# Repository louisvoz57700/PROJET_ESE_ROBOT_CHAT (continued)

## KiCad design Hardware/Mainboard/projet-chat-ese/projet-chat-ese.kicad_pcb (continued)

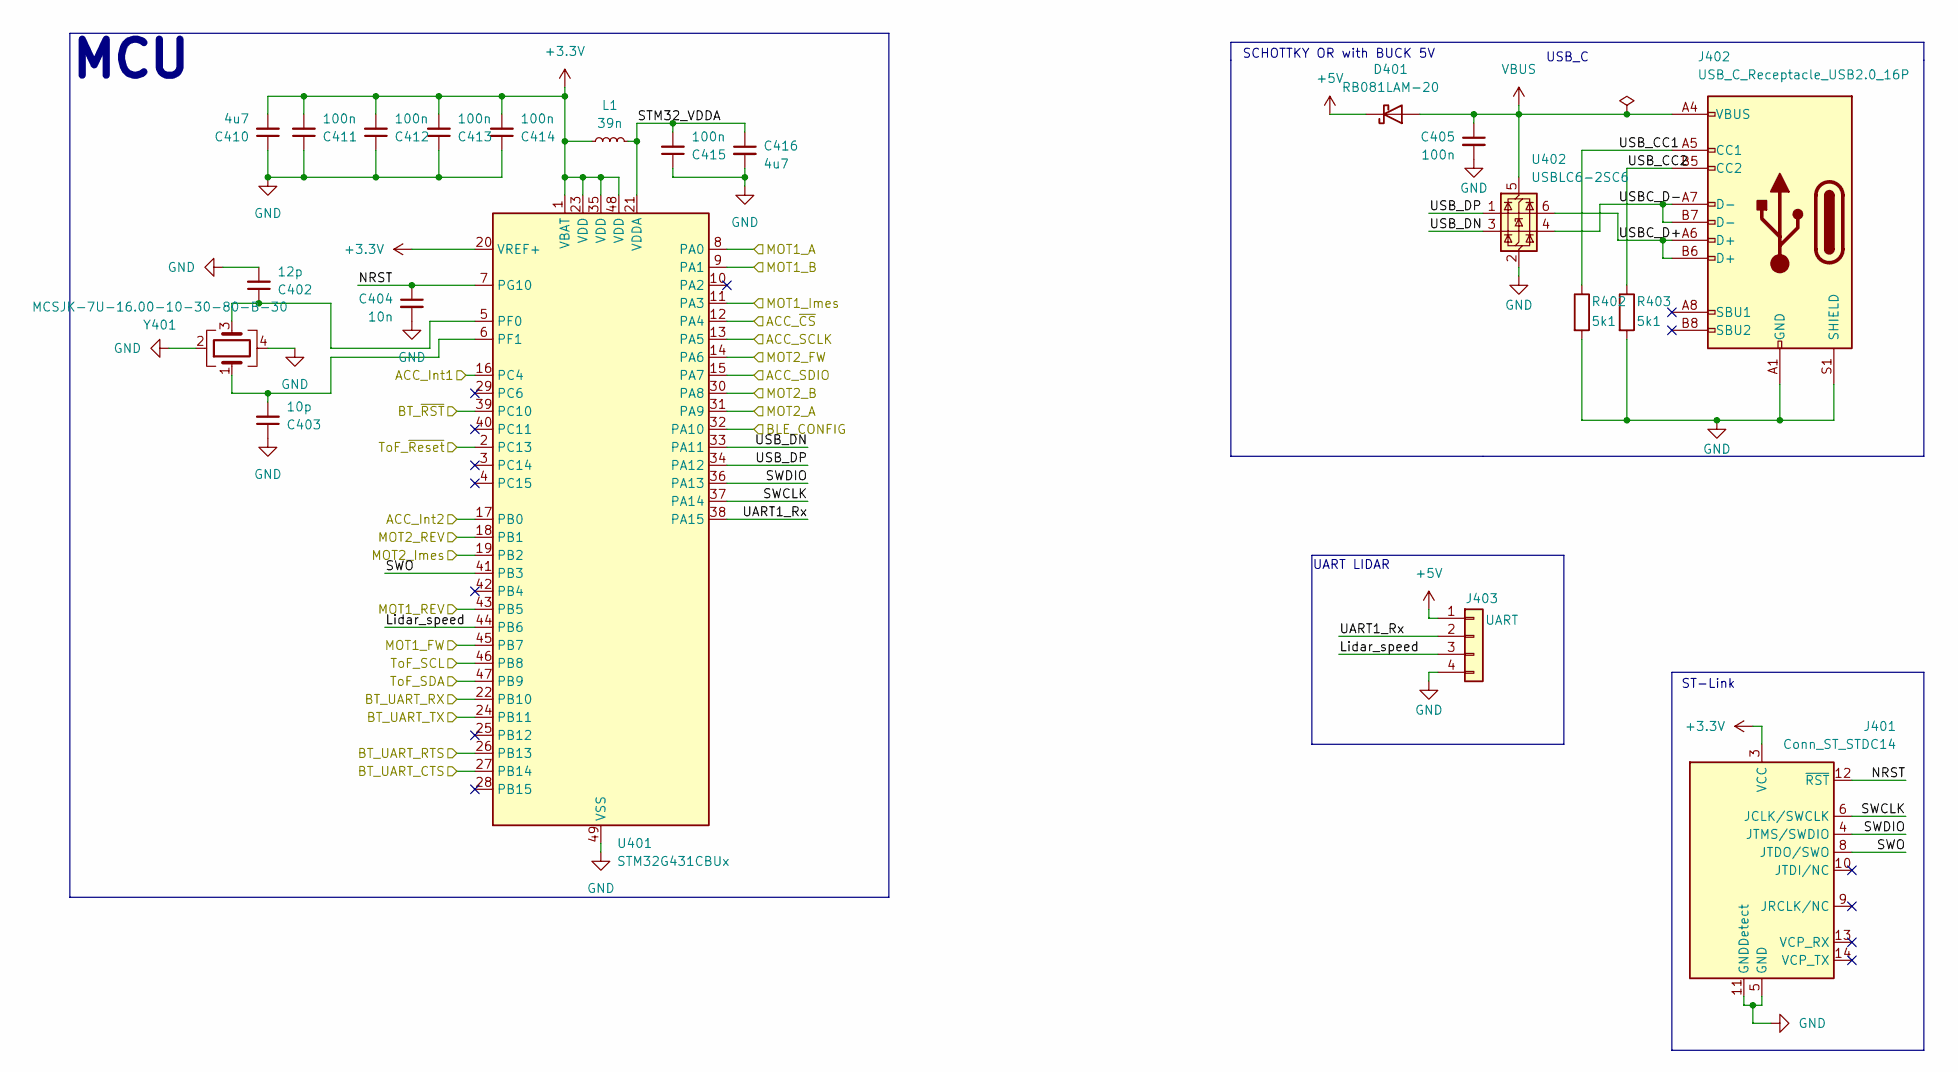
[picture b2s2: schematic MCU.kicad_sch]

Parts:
C402: 12p; C_0402_1005Metric
C403: 10p; C_0402_1005Metric
C404: 10n; C_0402_1005Metric
C405, C411, C412, C413, C414, C415: 100n; C_0402_1005Metric
C410, C416: 4u7; C_0402_1005Metric
D401: RB081LAM-20; D_SOD-128
J401: Conn_ST_STDC14; PinHeader_2x07_P1.27mm_Vertical_SMD
J402: USB_C_Receptacle_USB2.0_16P; USB_C_Receptacle_XKB_U262-16XN-4BVC11
J403: UART; JST_PH_B4B-PH-K_1x04_P2.00mm_Vertical
L1: 39n; L_0603_1608Metric
R402, R403: 5k1; R_0402_1005Metric
U401: STM32G431CBUx; QFN-48-1EP_7x7mm_P0.5mm_EP5.6x5.6mm
U402: USBLC6-2SC6; SOT-23-6
Y401: MCSJK-7U-16.00-10-30-80-B-30; SMD 3225

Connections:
+5V: D401.1 (K), J403.1; also elsewhere on the board
/Accelerometer/ACC_Int1: U401.16 (PC4); also elsewhere on the board
/Accelerometer/ACC_Int2: U401.17 (PB0); also elsewhere on the board
/Accelerometer/ACC_SCLK: U401.13 (PA5); also elsewhere on the board
/Accelerometer/ACC_SDIO: U401.15 (PA7); also elsewhere on the board
/Accelerometer/ACC_~CS: U401.12 (PA4); also elsewhere on the board
/BT_Module/BT_UART_CTS: U401.27 (PB14); also elsewhere on the board
/BT_Module/BT_UART_RTS: U401.26 (PB13); also elsewhere on the board
/BT_Module/BT_UART_RX: U401.22 (PB10); also elsewhere on the board
/BT_Module/BT_UART_TX: U401.24 (PB11); also elsewhere on the board
/BT_Module/BT_~RESET: U401.39 (PC10); also elsewhere on the board
/MCU/Lidar_speed: J403.3, U401.44 (PB6)
/MCU/MOT1_A: U401.8 (PA0); also elsewhere on the board
/MCU/MOT1_B: U401.9 (PA1); also elsewhere on the board
/MCU/MOT1_FW: U401.45 (PB7); also elsewhere on the board
/MCU/MOT1_Imes: U401.11 (PA3); also elsewhere on the board
/MCU/MOT1_REV: U401.43 (PB5); also elsewhere on the board
/MCU/MOT2_A: U401.31 (PA9); also elsewhere on the board
/MCU/MOT2_B: U401.30 (PA8); also elsewhere on the board
/MCU/MOT2_FW: U401.14 (PA6); also elsewhere on the board
/MCU/MOT2_Imes: U401.19 (PB2); also elsewhere on the board
/MCU/MOT2_REV: U401.18 (PB1); also elsewhere on the board
/MCU/NRST: C404.1, J401.12 (~RST), U401.7 (PG10)
/MCU/STM32_VDDA: C415.2, C416.1, L1.2, U401.21 (VDDA)
/MCU/SWCLK: J401.6 (JCLK/SWCLK), U401.37 (PA14)
/MCU/SWDIO: J401.4 (JTMS/SWDIO), U401.36 (PA13)
/MCU/SWO: J401.8 (JTDO/SWO), U401.41 (PB3)
/MCU/ToF_SCL: U401.46 (PB8); also elsewhere on the board
/MCU/ToF_SDA: U401.47 (PB9); also elsewhere on the board
/MCU/ToF_~Reset: U401.2 (PC13); also elsewhere on the board
/MCU/UART1_Rx: J403.2, U401.38 (PA15)
/MCU/USBC_D+: J402.A6 (D+), J402.B6 (D+), U402.6 (I/O1)
/MCU/USBC_D-: J402.A7 (D-), J402.B7 (D-), U402.4 (I/O2)
/MCU/USB_CC1: J402.A5 (CC1), R402.1
/MCU/USB_CC2: J402.B5 (CC2), R403.1
/MCU/USB_DN: U401.33 (PA11), U402.3 (I/O2)
/MCU/USB_DP: U401.34 (PA12), U402.1 (I/O1)
GND: C402.2, C403.1, C404.2, C405.2, C410.1, C411.1, C412.1, C413.1, C414.1, C415.1, C416.2, J401.5 (GND), J401.7 (GND), J401.11 (GNDDetect), J402.A1 (GND), J402.A12 (GND), J402.B1 (GND), J402.B12 (GND), J402.S1 (SHIELD), J403.4, R402.2, R403.2, U401.49 (VSS), U402.2 (GND), Y401.2, Y401.4; also elsewhere on the board
unnamed: C402.1, U401.5 (PF0), Y401.3
unnamed: C403.2, U401.6 (PF1), Y401.1
VBUS: C405.1, D401.2 (A), J402.A4 (VBUS), J402.A9 (VBUS), J402.B4 (VBUS), J402.B9 (VBUS), U402.5 (VBUS)

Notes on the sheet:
ST-Link
USB_C
SCHOTTKY OR with BUCK 5V
MCU
UART LIDAR

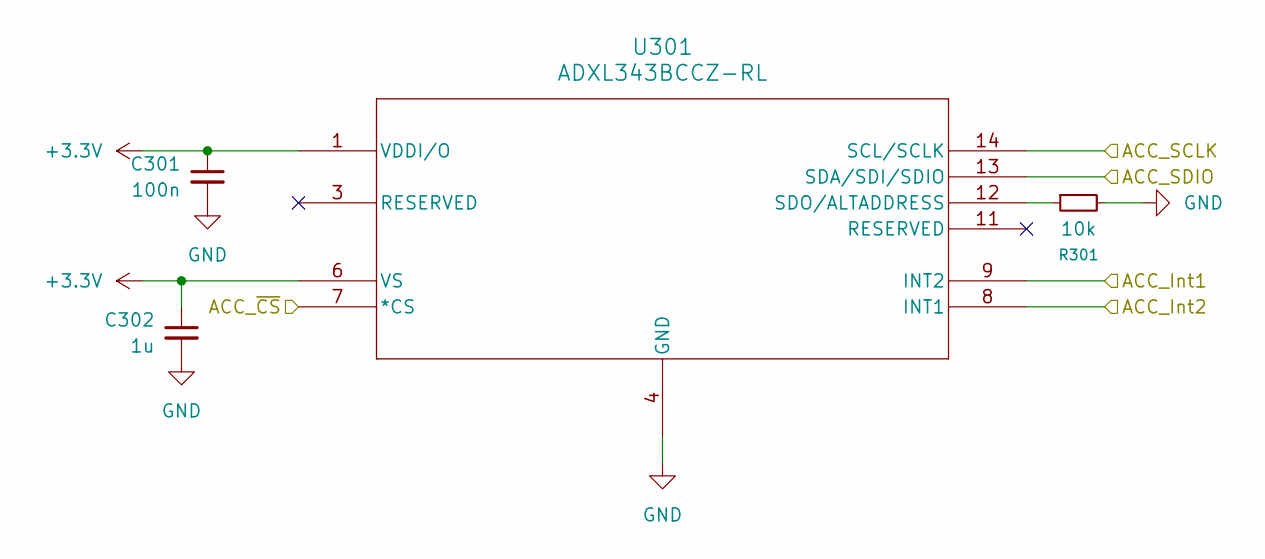
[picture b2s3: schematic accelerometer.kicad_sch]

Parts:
C301: 100n; C_0402_1005Metric
C302: 1u; C_0603_1608Metric
R301: 10k; R_0402_1005Metric
U301: ADXL343BCCZ-RL; LGA_CC-14-1_ADI

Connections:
/Accelerometer/ACC_Int1: U301.9 (INT2); also elsewhere on the board
/Accelerometer/ACC_Int2: U301.8 (INT1); also elsewhere on the board
/Accelerometer/ACC_SCLK: U301.14 (SCL/SCLK); also elsewhere on the board
/Accelerometer/ACC_SDIO: U301.13 (SDA/SDI/SDIO); also elsewhere on the board
/Accelerometer/ACC_~CS: U301.7 (*CS); also elsewhere on the board
GND: C301.2, C302.2, R301.2, U301.2 (GND), U301.4 (GND), U301.5 (GND); also elsewhere on the board
unnamed: R301.1, U301.12 (SDO/ALTADDRESS)

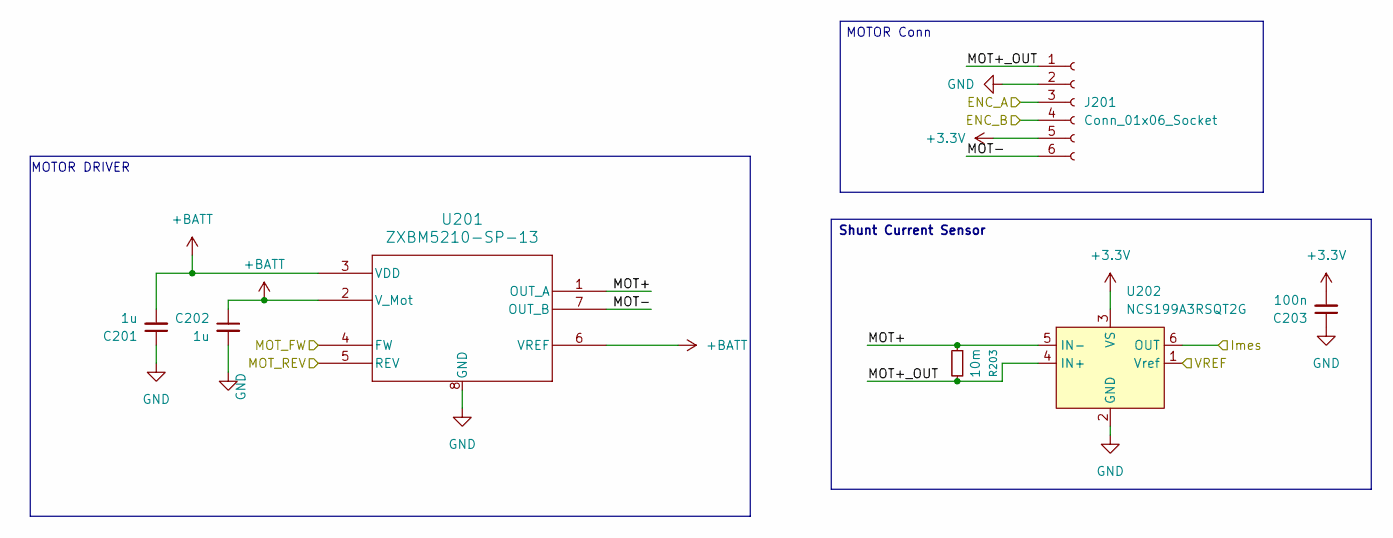
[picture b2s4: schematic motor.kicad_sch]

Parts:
C201, C202: 1u; C_0603_1608Metric
C203: 100n; C_0402_1005Metric
J201: Conn_01x06_Socket; JST_PH_B6B-PH-K_1x06_P2.00mm_Vertical
R203: 10m; R_0805_2012Metric; MPN 580 060 720 008
U201: ZXBM5210-SP-13; SOIC-8-1EP_3.9x4.9mm_P1.27mm_EP2.29x3mm
U202: NCS199A3RSQT2G; SC70-6

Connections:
+BATT: C201.2, C202.1, U201.2 (V_Mot), U201.3 (VDD), U201.6 (VREF); also elsewhere on the board
/MCU/MOT1_A: J201.3; also elsewhere on the board
/MCU/MOT1_B: J201.4; also elsewhere on the board
/MCU/MOT1_FW: U201.4 (FW); also elsewhere on the board
/MCU/MOT1_Imes: U202.6 (OUT); also elsewhere on the board
/MCU/MOT1_REV: U201.5 (REV); also elsewhere on the board
/MOTOR_VREF: U202.1 (Vref); also elsewhere on the board
/Motor Sheet/MOT+: R203.1, U201.1 (OUT_A), U202.5 (IN-)
/Motor Sheet/MOT+_OUT: J201.1, R203.2, U202.4 (IN+)
/Motor Sheet/MOT-: J201.6, U201.7 (OUT_B)
GND: C201.1, C202.2, C203.1, J201.2, U201.8 (GND), U201.9 (GND), U202.2 (GND); also elsewhere on the board

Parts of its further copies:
C204: 100n; C_0402_1005Metric
C601, C602: 1u; C_0603_1608Metric
J601: Conn_01x06_Socket; JST_PH_B6B-PH-K_1x06_P2.00mm_Vertical
R204: 10m; R_0805_2012Metric; MPN 580 060 720 008
U601: ZXBM5210-SP-13; SOIC-8-1EP_3.9x4.9mm_P1.27mm_EP2.29x3mm
U602: NCS199A3RSQT2G; SC70-6

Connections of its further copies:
+BATT: C601.2, C602.1, U601.2 (V_Mot), U601.3 (VDD), U601.6 (VREF); also elsewhere on the board
/MCU/MOT2_A: J601.3; also elsewhere on the board
/MCU/MOT2_B: J601.4; also elsewhere on the board
/MCU/MOT2_FW: U601.4 (FW); also elsewhere on the board
/MCU/MOT2_Imes: U602.6 (OUT); also elsewhere on the board
/MCU/MOT2_REV: U601.5 (REV); also elsewhere on the board
/MOTOR_VREF: U602.1 (Vref); also elsewhere on the board
/Motor Sheet1/MOT+: R204.1, U601.1 (OUT_A), U602.5 (IN-)
/Motor Sheet1/MOT+_OUT: J601.1, R204.2, U602.4 (IN+)
/Motor Sheet1/MOT-: J601.6, U601.7 (OUT_B)
GND: C204.1, C601.1, C602.2, J601.2, U601.8 (GND), U601.9 (GND), U602.2 (GND); also elsewhere on the board

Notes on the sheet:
MOTOR DRIVER
Shunt Current Sensor
MOTOR Conn

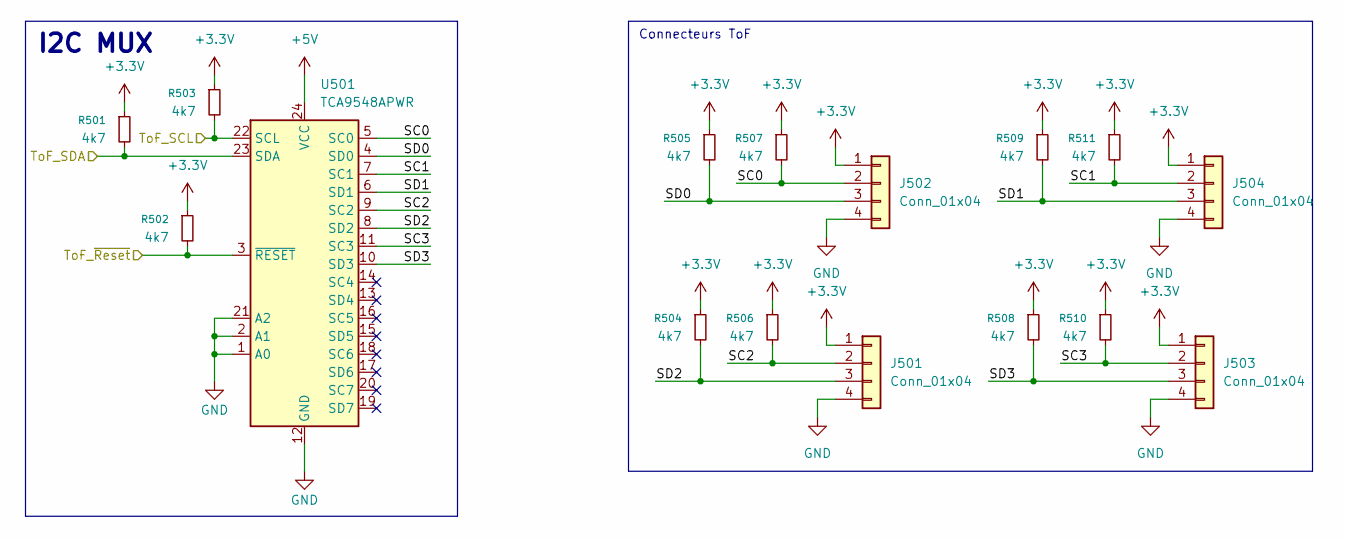
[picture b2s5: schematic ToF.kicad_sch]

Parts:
J501, J502, J503, J504: Conn_01x04; JST_PH_B4B-PH-K_1x04_P2.00mm_Vertical
R501, R502, R503, R504, R505, R506, R507, R508, R509, R510, R511: 4k7; R_0402_1005Metric
U501: TCA9548APWR; VQFN-24-1EP_4x4mm_P0.5mm_EP2.45x2.45mm

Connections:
+5V: U501.24 (VCC); also elsewhere on the board
/MCU/ToF_SCL: R503.2, U501.22 (SCL); also elsewhere on the board
/MCU/ToF_SDA: R501.2, U501.23 (SDA); also elsewhere on the board
/MCU/ToF_~Reset: R502.2, U501.3 (~RESET); also elsewhere on the board
/ToF/SC0: J502.2, R507.2, U501.5 (SC0)
/ToF/SC1: J504.2, R511.2, U501.7 (SC1)
/ToF/SC2: J501.2, R506.2, U501.9 (SC2)
/ToF/SC3: J503.2, R510.2, U501.11 (SC3)
/ToF/SD0: J502.3, R505.2, U501.4 (SD0)
/ToF/SD1: J504.3, R509.2, U501.6 (SD1)
/ToF/SD2: J501.3, R504.2, U501.8 (SD2)
/ToF/SD3: J503.3, R508.2, U501.10 (SD3)
GND: J501.4, J502.4, J503.4, J504.4, U501.1 (A0), U501.2 (A1), U501.12 (GND), U501.21 (A2), U501.25 (PAD); also elsewhere on the board

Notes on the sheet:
I2C MUX
Connecteurs ToF

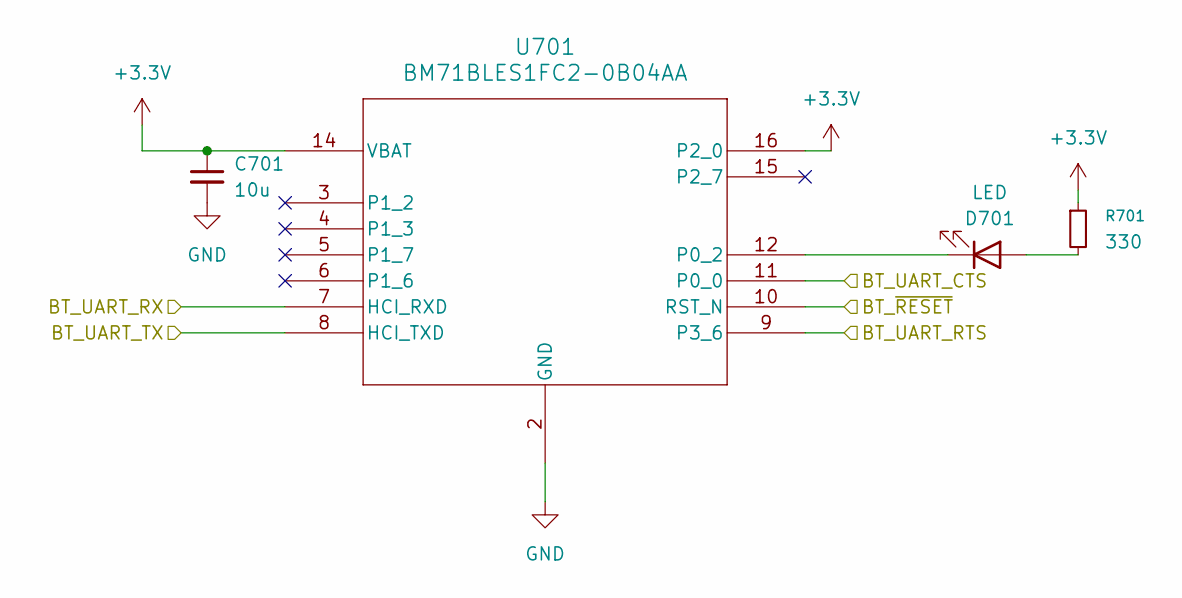
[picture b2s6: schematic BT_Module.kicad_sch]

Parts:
C701: 10u; C_0805_2012Metric
D701: LED; LED_0603_1608Metric
R701: 330; R_0402_1005Metric
U701: BM71BLES1FC2-0B04AA; BM71BLES1FC2_MCH

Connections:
/BT_Module/BT_UART_CTS: U701.11 (P0_0); also elsewhere on the board
/BT_Module/BT_UART_RTS: U701.9 (P3_6); also elsewhere on the board
/BT_Module/BT_UART_RX: U701.7 (HCI_RXD); also elsewhere on the board
/BT_Module/BT_UART_TX: U701.8 (HCI_TXD); also elsewhere on the board
/BT_Module/BT_~RESET: U701.10 (RST_N); also elsewhere on the board
GND: C701.2, U701.2 (GND), U701.13 (GND); also elsewhere on the board
unnamed: D701.2 (A), R701.2
unnamed: D701.1 (K), U701.12 (P0_2)

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
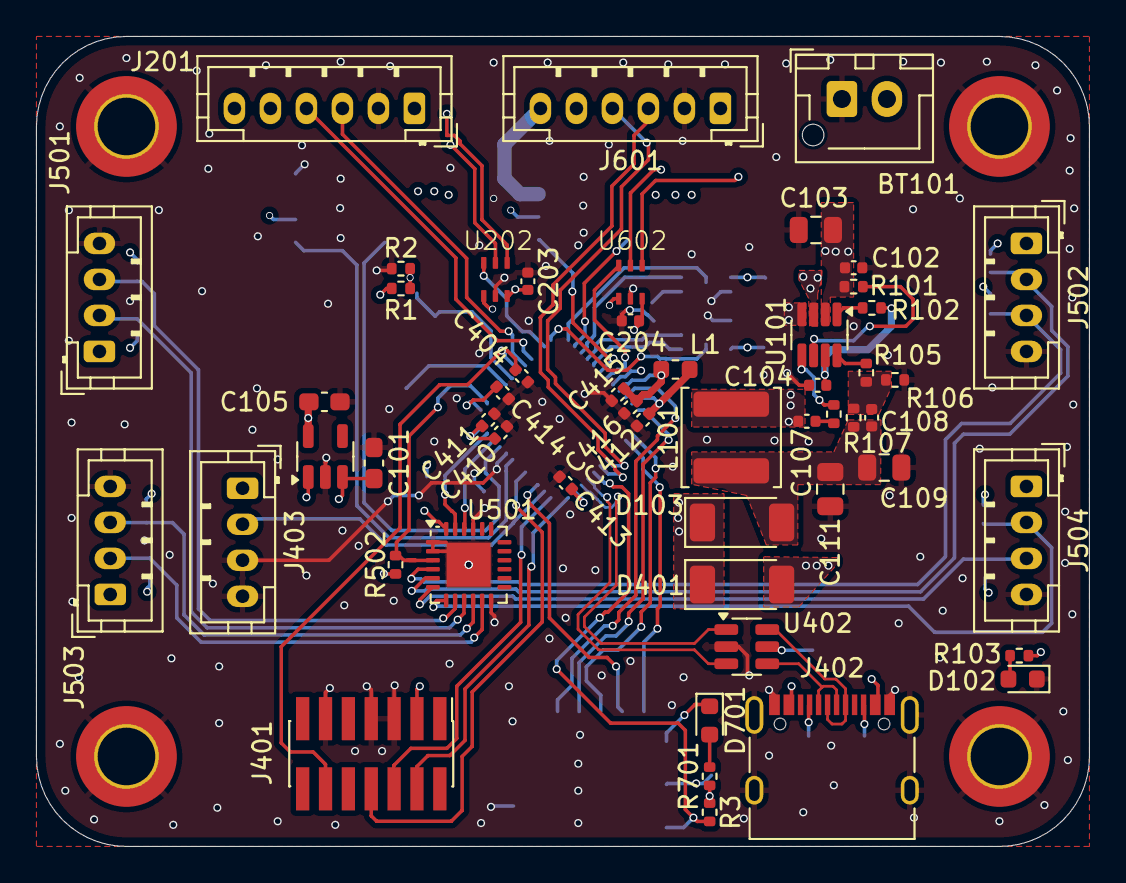
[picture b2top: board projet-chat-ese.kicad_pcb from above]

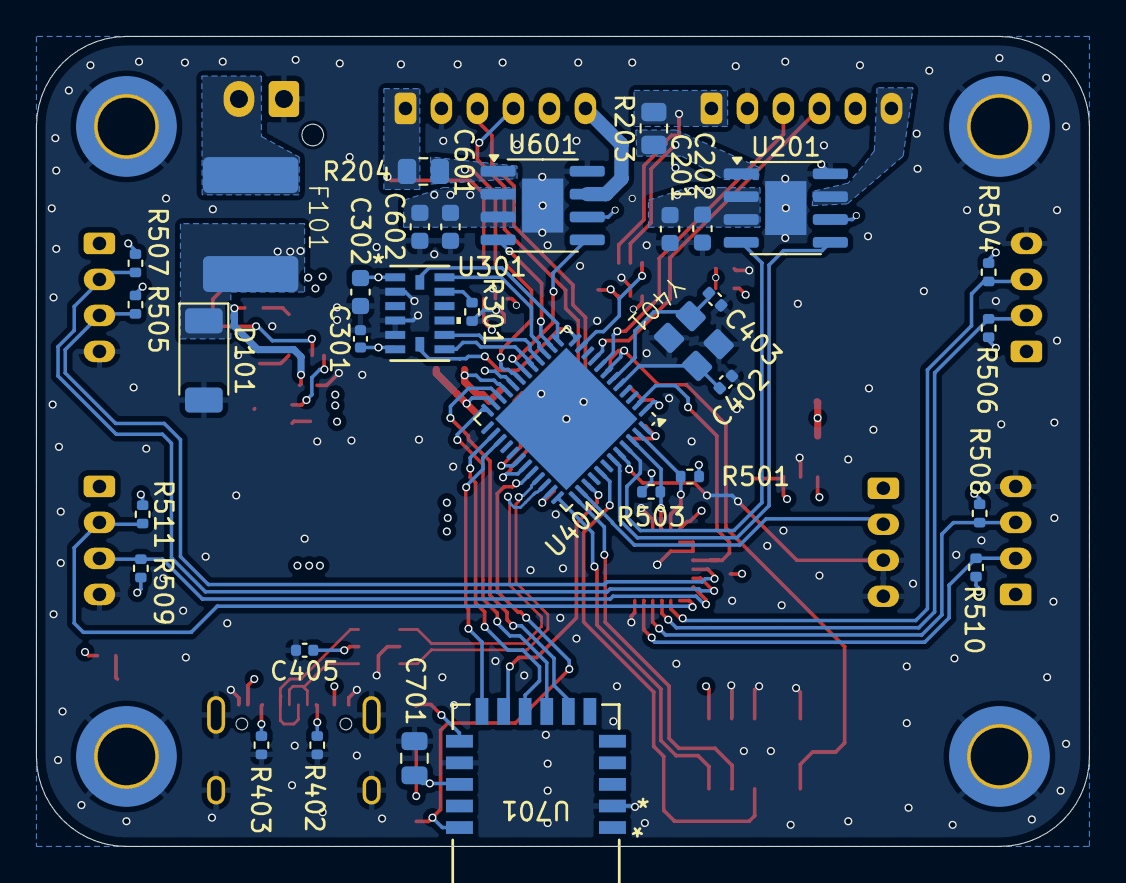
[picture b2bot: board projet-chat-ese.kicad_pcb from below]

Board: 4 copper layers, 58.5 x 45.0 mm, 90 parts (33 on the bottom side), 73 nets.

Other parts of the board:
R3: 100k; R_0402_1005Metric

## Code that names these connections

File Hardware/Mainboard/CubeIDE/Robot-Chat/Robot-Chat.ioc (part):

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Mcu.Name=STM32G431C(6-8-B)Ux
Mcu.Package=UFQFPN48
Mcu.UserName=STM32G431CBUx
PA0.GPIOParameters=GPIO_Label
PA0.GPIO_Label=ENC1_A
PA0.Signal=S_TIM2_CH1
PA1.GPIOParameters=GPIO_Label
PA1.GPIO_Label=ENC1_B
PA1.Signal=S_TIM2_CH2
PA10.GPIOParameters=GPIO_Label
PA10.GPIO_Label=BT_Config
PA10.Signal=GPIO_Output
PA11.Mode=Device
PA11.Signal=USB_DM
PA12.Mode=Device
PA12.Signal=USB_DP
PA13.Mode=Trace_Asynchronous_SW
PA13.Signal=SYS_JTMS-SWDIO
PA14.Mode=Trace_Asynchronous_SW
PA14.Signal=SYS_JTCK-SWCLK
PA15.Mode=Asynchronous
PA15.Signal=USART2_RX
PA2.Mode=Asynchronous
PA2.Signal=USART2_TX
PA3.GPIOParameters=GPIO_Label
PA3.GPIO_Label=MOT1_Imes
PA3.Mode=IN4-Single-Ended
PA3.Signal=ADC1_IN4
PA4.Mode=NSS_Signal_Hard_Output
PA4.Signal=SPI1_NSS
PA5.Mode=Simplex_Bidirectional_Master
PA5.Signal=SPI1_SCK
PA6.GPIOParameters=GPIO_Label
PA6.GPIO_Label=MOT2_FW
PA6.Signal=S_TIM3_CH1
PA7.Mode=Simplex_Bidirectional_Master
PA7.Signal=SPI1_MOSI
PA8.GPIOParameters=GPIO_Label
PA8.GPIO_Label=ENC2_B
PA8.Signal=S_TIM1_CH1
PA9.GPIOParameters=GPIO_Label
PA9.GPIO_Label=ENC2_A
PA9.Signal=S_TIM1_CH2
PB0.GPIOParameters=GPIO_Label
PB0.GPIO_Label=ACC_INT2
PB0.Signal=GPXTI0
PB1.GPIOParameters=GPIO_Label
PB1.GPIO_Label=MOT2_REV
PB1.Signal=S_TIM3_CH4
PB10.Mode=Asynchronous
PB10.Signal=USART3_TX
PB11.Mode=Asynchronous
PB11.Signal=USART3_RX
PB13.Mode=CTS_RTS
PB13.Signal=USART3_CTS
PB14.Mode=CTS_RTS
PB14.Signal=USART3_RTS
PB2.GPIOParameters=GPIO_Label
PB2.GPIO_Label=MOT2_Imes
PB2.Mode=IN12-Single-Ended
PB2.Signal=ADC2_IN12
PB3.Mode=Trace_Asynchronous_SW
PB3.Signal=SYS_JTDO-SWO
PB5.GPIOParameters=GPIO_Label
PB5.GPIO_Label=MOT1_REV
PB5.Signal=S_TIM3_CH2
PB6.GPIOParameters=GPIO_Label
PB6.GPIO_Label=Lidar_Speed_PWM
PB6.Signal=S_TIM8_CH1
PB7.GPIOParameters=GPIO_Label
PB7.GPIO_Label=MOT1_FW\!
PB7.Signal=S_TIM4_CH2
PB8-BOOT0.Mode=I2C
PB8-BOOT0.Signal=I2C1_SCL
PB9.Mode=I2C
PB9.Signal=I2C1_SDA
PC10.GPIOParameters=GPIO_Label
PC10.GPIO_Label=BT_nRST
PC10.Signal=GPIO_Output
PC13.GPIOParameters=GPIO_Label
PC13.GPIO_Label=ToF_nRST
PC13.Signal=GPIO_Output
PC4.GPIOParameters=GPIO_Label
PC4.GPIO_Label=ACC_INT1
PC4.Signal=GPXTI4
PF0-OSC_IN.Mode=HSE-External-Oscillator
PF0-OSC_IN.Signal=RCC_OSC_IN
PF1-OSC_OUT.Mode=HSE-External-Oscillator
PF1-OSC_OUT.Signal=RCC_OSC_OUT
RCC.HSE_VALUE=16000000
RCC.SYSCLKFreq_VALUE=144000000
RCC.SYSCLKSource=RCC_SYSCLKSOURCE_PLLCLK
board=custom

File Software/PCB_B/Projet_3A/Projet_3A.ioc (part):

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Mcu.Name=STM32WB55CGUx
Mcu.Package=UFQFPN48
Mcu.UserName=STM32WB55CGUx
PA0.GPIOParameters=GPIO_Label
PA0.GPIO_Label=ENC_A_M2
PA0.Signal=S_TIM2_CH1
PA1.GPIOParameters=GPIO_Label
PA1.GPIO_Label=ENC_B_M2
PA1.Signal=S_TIM2_CH2
PA10.GPIOParameters=GPIO_Label
PA10.GPIO_Label=PWM_1_M1
PA10.Signal=S_TIM1_CH3
PA11.GPIOParameters=GPIO_Label
PA11.GPIO_Label=PWM_2_M1
PA11.Signal=S_TIM1_CH4
PA13.Mode=Trace_Asynchronous_SW
PA13.Signal=SYS_JTMS-SWDIO
PA14.Mode=Trace_Asynchronous_SW
PA14.Signal=SYS_JTCK-SWCLK
PA2.GPIOParameters=GPIO_Label
PA2.GPIO_Label=STATE_LED_1
PA2.Signal=GPIO_Output
PA3.GPIOParameters=GPIO_Label
PA3.GPIO_Label=STATE_LED_2
PA3.Signal=GPIO_Output
PA4.GPIOParameters=GPIO_Label
PA4.GPIO_Label=I_BAT
PA4.Signal=ADCx_IN9
PA5.GPIOParameters=GPIO_Label
PA5.GPIO_Label=V_BAT
PA5.Signal=ADCx_IN10
PA6.GPIOParameters=GPIO_Label
PA6.GPIO_Label=PWM_1_M2
PA6.Signal=S_TIM16_CH1
PA7.GPIOParameters=GPIO_Label
PA7.GPIO_Label=PWM_2_M2
PA7.Signal=S_TIM17_CH1
PA8.GPIOParameters=GPIO_Label
PA8.GPIO_Label=ENC_A_M1
PA8.Signal=S_TIM1_CH1
PA9.GPIOParameters=GPIO_Label
PA9.GPIO_Label=ENC_B_M1
PA9.Signal=S_TIM1_CH2
PB0.GPIOParameters=GPIO_Label
PB0.GPIO_Label=SINGLE_TAP
PB0.Signal=GPXTI0
PB1.GPIOParameters=GPIO_Label
PB1.GPIO_Label=INT_2
PB1.Signal=GPXTI1
PB3.Mode=Trace_Asynchronous_SW
PB3.Signal=SYS_JTDO-SWO
PB4.Signal=GPIO_Output
PB6.Mode=Asynchronous
PB6.Signal=USART1_TX
PB7.Mode=Asynchronous
PB7.Signal=USART1_RX
PB8.Mode=I2C
PB8.Signal=I2C1_SCL
PB9.Mode=I2C
PB9.Signal=I2C1_SDA
PC14-OSC32_IN.Mode=LSE-External-Oscillator
PC14-OSC32_IN.Signal=RCC_OSC32_IN
PC15-OSC32_OUT.Mode=LSE-External-Oscillator
PC15-OSC32_OUT.Signal=RCC_OSC32_OUT
RCC.HSE_VALUE=32000000
RCC.SYSCLKFreq_VALUE=32000000
board=custom

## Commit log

2025-09-09 Creation du KiCad
2025-09-11 MAJ Datasheet
2025-09-12 [Update] PCB
2025-09-19 KSA : PCB G431 :
2025-09-24 On a pas de wiork trtee anyway
2025-09-24 MAJ_PCB_BLE
2025-09-24 MAJ PCB
2025-09-24 projet cube ide bluetooth, tel vers st
2025-09-24 MAJ_SILKSCREEN
2025-09-25 Finishing PCB
2025-09-25 PCB G431 details
2025-09-27 code STM Bluetooth envoie et réception de données
2025-09-29 MODIF PCB ( NEW TIMER )
2025-09-30 code STM Bluetooth envoie et réception de données et scanf
2025-09-30 code STM écran oled
2025-09-30 Test ACCelero
2025-10-01 MAJ FOLDER
2025-10-01 code STM écran oled avec changement d'images avec bouton
2025-10-01 Updating silkscreen on pcb
2025-10-01 check pcb kenny LF
2025-10-01 Last PCB edits G431
2025-10-01 G431 PCB Final
2025-10-01 G431
2025-10-01 code STM32WB communication avec un pc
2025-10-01 app pc
2025-10-01 CODE LIDAR
2025-10-04 app BLE read and write + IHM
2025-11-12 freertos code + driver
2025-11-12 separataion des .c .h
2025-11-12 code STM écran et FreeRTOS
2025-11-26 Kenny's Last work
2025-12-02 odom_pid
2025-12-02 algo decision
2025-12-02 update lidar
2025-12-05 PID corrigé
2025-12-09 Structure de taches
2025-12-10 mode souris opérationel
2025-12-10 editing odometry data
2025-12-10 oupsie
2025-12-10 schematic update
2025-12-11 update tof + lidar
2025-12-16 .c et .h
2025-12-16 code souris_toff
2025-12-16 integrationII
2025-12-16 evade +tof fsm
2025-12-16 integration No warnings
2026-01-02 gitignore
2026-01-02 clean
2026-01-02 photos
2026-01-08 tony_merged, plus d'erreurs
2026-01-09 tony_merged_2
2026-01-09 tony_and_co
2026-01-09 version_finale_chat
2026-01-18 jeu_chat
2026-01-18 updating PCB documentations
2026-01-18 preuve_BLE
2026-01-19 upd rdme
2026-01-19 slkskl
2026-01-21 Fix link path for Bluetooth code reference
    Updated link path for Bluetooth proof code in README.
2026-01-21 Update README with Bluetooth and FreeRTOS sections
    Added sections for Bluetooth and FreeRTOS in README.
2026-01-22 Add width and height attributes to images in README
    Updated image tag to include width and height attributes.
2026-01-22 Fix image formatting in README.md
    Updated image links in the README for better formatting.
2026-01-22 Fix image formatting in README.md
2026-01-22 Updates on the ReadMe
    Updated project phases with detailed descriptions and timelines. Removed the To-Do List and session summaries for clarity.
2026-01-22 Fix formatting issues in README.md
    Correct formatting and spacing in the README.
2026-01-22 Adjust image size in README.md
    Updated image dimensions in the README file.
2026-01-22 Fix image width in README.md
    Updated image width in the principle schema section.
2026-01-22 Revise project goals and organization details
    Updated project objectives and organization phases in README.
2026-01-22 Rename pcb.md to README.md
2026-01-22 Add initial content to README.md
2026-01-22 Add x.png image to Hardware/WB55 directory
2026-01-22 Rename Hardware/image-1.png to Hardware/images/image-1.png
2026-01-22 Rename Hardware/images/image-1.png to Hardware/WB55/images/image-1.png
2026-01-22 Rename Hardware/image-2.png to Hardware/WB55/images/image-2.png
2026-01-22 Rename Hardware/image.png to Hardware/WB55/images/image.png
2026-01-22 Enhance README with PCB Bluetooth details
    Added detailed information about the PCB Bluetooth components and features.
2026-01-22 Update images in README for WB55 hardware
2026-01-22 Update README links for hardware and software sections
2026-01-23 Tidyinn up the readme
    Removed the 'Schéma de Principe' section from the README.
2026-01-23 Update README with principle diagram and images
    Added principle diagram and PCB realization images.
2026-01-23 Update README with decision flowchart and sensor info
    Added decision flowchart and updated sensor and actuator sections.
2026-01-23 Update README with connection instructions
2026-01-23 Remove an image from Software/README.md
    Removed an image from the README file.
2026-01-23 Add results section to README with video link
    Added results section with video link of autonomous robot.
2026-01-23 Add Bluetooth section to README
    Updated README with Bluetooth section details.
2026-01-23 Revise video link and clean up README formatting
    Updated video link and removed an empty line in the README.
2026-01-23 Fix typo in README about mouse game management
    Corrected a typo in the README regarding mouse game management.
2026-01-25 IHM demonstration and readme update in Software
